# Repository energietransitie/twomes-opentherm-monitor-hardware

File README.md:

# Twomes OpenTherm Monitor Shield hardware

This repository contains the open hardware design files for the Twomes OpenTherm Monitor device, consisting of:
* a Twomes OpenTherm Monitor Shield with a [WeMos D1 Mini shield](https://www.wemos.cc/en/latest/d1_mini_shield/index.html) form factor, to be placed on;
* a WeMos D1 Mini board, such as the [LilyGO TTGO T7 Mini32 V1.3 ESP32](https://github.com/LilyGO/ESP32-MINI-32-V1.3). 

The OpenTherm Monitor Shield is connected via one pluggable terminal block with screws to connect one wire pair leading to a [boiler that supports OpenTherm](https://www.otgw.tclcode.com/matrix.cgi#boilers) and via another one pluggable terminal block with screws to connect another wire pair leading to a [thermostat that supports OpenTherm](https://www.otgw.tclcode.com/matrix.cgi#thermostats). The Twomes OpenTherm Monitor can upload this measurement data to a Twomes server via Wi-Fi using secure HTTPS.

N.B. This is device  is NOT an OpenTherm gateway; it only monitors OpenTherm traffic and it cannot insert OpenTherm commands to the boiler or thermostat.

## Table of contents
* [General info](#general-info)
* [Producing](#producing)
* [Developing](#developing) 
* [Features](#features)
* [Status](#status)
* [License](#license)
* [Citation](#citation)
* [Credits](#credits)

## General info
This repository contains the open hardware designs files for the Twomes OpenTherm Monitor device, It also includes a `docs` folder with recent printouts of the [schematics](./docs/twomes-opentherm-monitor-hardware-sch-v2.0.pdf) and [PCB layout](./docs/twomes-opentherm-monitor-hardware-pcb-v2.0.pdf). 

The associated firmware that you can run on this device can be found in [this repository](https://github.com/energietransitie/twomes-opentherm-monitor-firmware).

## Producing

### Printed Ciruit Board
To fabricate the printed circuit board you can use various PCB services. 

The folder [pcb/jlcpcb](./pcb/jlcpcb) includes all exported files needed to have the PCBs manufactured by [JLCPCB](https://www.jlcpcb.com). Upload the [zipped gerber files](./pcb/jlcpcb/gerber/gerber-OpenThermMonitorTwomes.zip) to the [JLCPCB quote page](https://cart.jlcpcb.com/quote), select the amount of PCBs and a colour for the silkscreen. All other options can be left on default. If SMT assembly is desired, also select this option before ordering. This will take you to a page where the BOM and POS file can be uploaded. Use the files [BOM-TwomesGateway.csv](./pcb/jlcpcb/assembly/BOM-Twomes-OpenTherm-Monitor.csv) and [CPL-TwomesGateway.csv](./pcb/jlcpcb/assembly/CPL-Twomes-OpenTherm-Monitor.csv).

N.B. The pluggable terminal blocks we used (see [features](#features) are not listed the BOM-*.csv file; they need to be ordered separately other services and soldered manually.

### Enclosure
To fabricate the enclosure you can use your own 3D printer or use a 3D printing service. 

The folder [enclosure/fabrication](./enclosure/fabrication) contains exported STL files for the [case](./enclosure/fabrication/twomes-opentherm-monitor-enclosure-case.stl) and [lid](./enclosure/twomes-opentherm-monitor-enclosure-lid.stl) of the Twomes OpenTherm Monitor. The STL files can be imported into any slicer and turned into G-Code for a 3D printer.

## Developing

### Printed Circuit Board
To change the hardware design of the PCB, you need:
* [KiCad](https://www.kicad.org/download/) installed to change te PCB design. 

The KiCad source files of the PCB can be found in the folder [pcb](./pcb).

To convert the PCBs into a format suitable for fabrication, consult the webpage of your PCB manufacturer of choice. For example, see the [JLCPCB guide on how to export Gerbers](https://support.jlcpcb.com/article/149-how-to-generate-gerber-and-drill-files-in-kicad) and the  [JLCPCB guide how to export the BOM and POS files](https://support.jlcpcb.com/article/84-how-to-generate-the-bom-and-centroid-file-from-kicad). You may also use a KiCad plug-in for this purpose such as [kicad-jlcpcb-tools](https://github.com/Bouni/kicad-jlcpcb-tools).

### Enclosure
To change the hardware design of the enclosure, you need either:
* [Autodesk Fusion 360](https://www.kicad.org/download/) installed (Autodesk provides 30 day free trials and [free one-year educational access](https://www.autodesk.com/education/edu-software/overview?sorting=featured&filters=individual) to its products and services for eligible students, teachers and research staff); 
* or [FreeCAD](https://www.freecadweb.org/), an open source alternative.

The source files of the enclosure can be found in the folder [enclosure](./enclosure). We include both .f3d source files and .step source files we obtained after conversion.

## Features
The Twomes OpenTherm Monitor Shield is a [WeMos D1 Mini shield](https://www.wemos.cc/en/latest/d1_mini_shield/index.html) that features the following main hardware components:
* two terminal blocks [CTB9209/2](https://nl.farnell.com/camdenboss/ctb9209-2/terminal-block-pluggable-2pos/dp/2493642), pluggable into terminal block headers [CTB9359/2](https://nl.farnell.com/camdenboss/ctb9359-2/terminal-block-header-2pos-th/dp/2493694) (one for thermostat, one for boiler), each with two positions;
* two optocouplers that electrically separate the OpenTherm circuit on the shield from the monitoring logic on the shield and the main board: the OpenTherm communication between thermostat and boiler still works even if the main board receives no power via its micro USB port or has crashed;
* recessed button that is positioned behind a pinhole in the device enclosure, which allows the end-user to do a Wi-Fi reset.

To-do:
* change design and JLCPCB files to take advantage of the new [one-sided hand-soldering option for through-hole parts](https://jlcpcb.com/smt-assembly) for the pluggable terminal blocks `J1` and `J2` and the pin headers `P1` and `P2`;

## Status
Project is: _in progress_

## License
The hardware designs in this repository are available under the [CERN-OHL-P v2 license](./LICENSE), Copyright 2022 [Research group Energy Transition, Windesheim University of Applied Sciences](https://windesheim.nl/energietransitie)

## Citation

If you use this repository in your research or work, please cite the following pre-print, which describes the overall NeedForHeat DataGear system of which this repository is a part:

> Ter Hofte, H., & van Ravenzwaaij, N. (2025). *NeedForHeat DataGear: An Open Monitoring System to Accelerate the Residential Heating Transition*. arXiv preprint arXiv:2509.06927. https://doi.org/10.48550/arXiv.2509.06927

**Note:** This is a pre-print submitted on 8 Sep 2025 and has not yet been peer-reviewed. For the full paper, see [https://arxiv.org/abs/2509.06927](https://arxiv.org/abs/2509.06927).

## Credits
This open hardware design is a collaborative effort of:
* Marco Winkelman · [@MarcoW71](https://github.com/MarcoW71)
* Sjors Smit · [@Shorts1999](https://github.com/Shorts1999)

Thanks also go to:
* Henri ter Hofte · [@henriterhofte](https://github.com/henriterhofte)
We use and gratefully acknowlegde the efforts of the makers of the following designs:

* [KiCad Libraries](https://kicad.github.io/), by the KiCad Development Team, licensed under [an adapted version of the CC-BY-SA 4.0 License](https://www.kicad.org/libraries/license/)
* [Opentherm-monitor](https://www.domoticaforum.eu/uploaded/bwired/Open-Termostaat.pdf). In <i>Elektuur, 7-8/2001, pp. 22-23.

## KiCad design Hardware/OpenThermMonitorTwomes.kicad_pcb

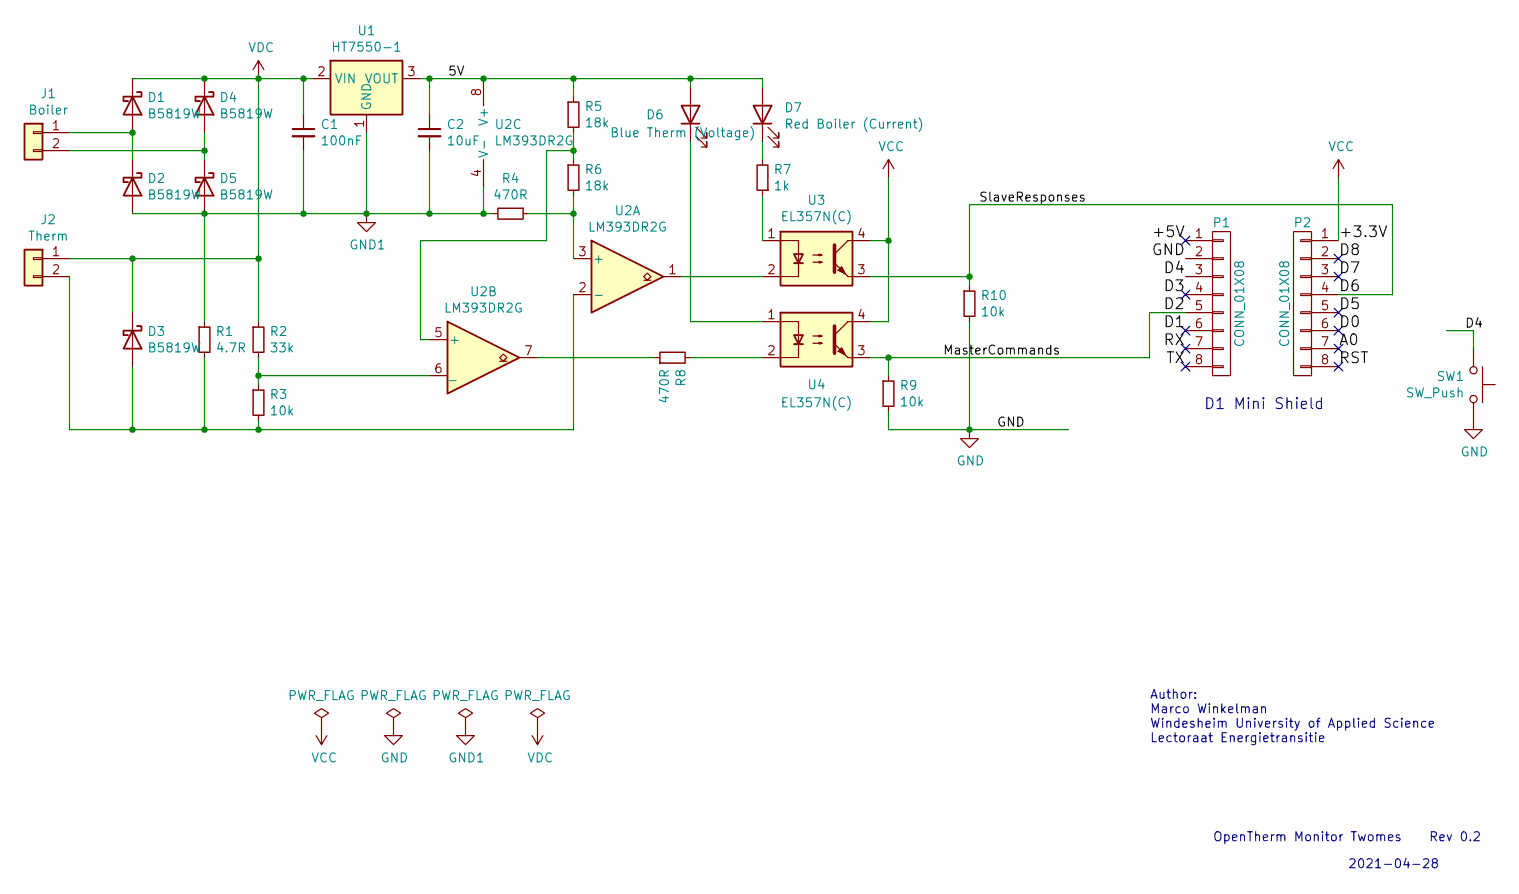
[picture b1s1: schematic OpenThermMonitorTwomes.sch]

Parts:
C1: 100nF; C_0603_1608Metric; LCSC C14663
C2: 10uF; C_0603_1608Metric; LCSC C19702
D1, D2, D3, D4, D5: B5819W; D_SOD-123; LCSC C8598
D6: Blue Therm (Voltage); LED_0805_2012Metric; LCSC C2293
D7: Red Boiler (Current); LED_0805_2012Metric; LCSC C84256
J1: Boiler; TerminalBlock_Phoenix_MKDS-1,5-2_1x02_P5.00mm_Horizontal
J2: Therm; TerminalBlock_Phoenix_MKDS-1,5-2_1x02_P5.00mm_Horizontal
P1, P2: CONN_01X08; D1_mini_Pin_Header
R1: 4.7R; R_0603_1608Metric; LCSC C23164
R2: 33k; R_0603_1608Metric; LCSC C4216
R3, R9, R10: 10k; R_0603_1608Metric; LCSC C25804
R4, R8: 470R; R_0603_1608Metric; LCSC C23179
R5, R6: 18k; R_0603_1608Metric; LCSC C25810
R7: 1k; R_0603_1608Metric; LCSC C21190
SW1: SW_Push; SW_SPST_EVQP7C; LCSC C115361
U1: HT7550-1; SOT-89-3; LCSC C16106
U2: LM393DR2G; SOIC-8_3.9x4.9mm_P1.27mm; LCSC C7955
U3, U4: EL357N(C); SO-4_4.4x3.6mm_P2.54mm; LCSC C29981

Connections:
/5V: C2.1, D6.2 (A), D7.2 (A), R5.1, U1.3 (VOUT), U2.8 (V+)
/+5V: P1.1
/A0: P2.7
/D0: P2.6
/D1: P1.6
/D2: P1.5, R9.1, U4.3
/D3: P1.4
/D4: P1.3, SW1.2
/D5: P2.5
/D6: P2.4, R10.1, U3.3
/D7: P2.3
/D8: P2.2
/RST: P2.8
/RX: P1.7
/TX: P1.8
GND: P1.2, R9.2, R10.2, SW1.1
GND1: C1.2, C2.2, D2.2 (A), D5.2 (A), R1.1, R4.2, U1.1 (GND), U2.4 (V-)
unnamed: D1.2 (A), D2.1 (K), J1.1
unnamed: D3.2 (A), J2.2, R1.2, R3.2, U2.2 (-)
unnamed: D4.2 (A), D5.1 (K), J1.2
unnamed: D6.1 (K), U4.1
unnamed: D7.1 (K), R7.2
unnamed: R2.2, R3.1, U2.6 (_)
unnamed: R4.1, R6.2, U2.3 (+)
unnamed: R5.2, R6.1, U2.5 (+)
unnamed: R7.1, U3.1
unnamed: R8.1, U2.7
unnamed: R8.2, U4.2
unnamed: U2.1, U3.2
VCC: P2.1, U3.4, U4.4
VDC: C1.1, D1.1 (K), D3.1 (K), D4.1 (K), J2.1, R2.1, U1.2 (VIN)

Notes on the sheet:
D1 Mini Shield
OpenTherm Monitor Twomes
Author: Marco Winkelman Windesheim University of Applied Science Lectoraat Energietransitie
2021-04-28
Rev 0.2

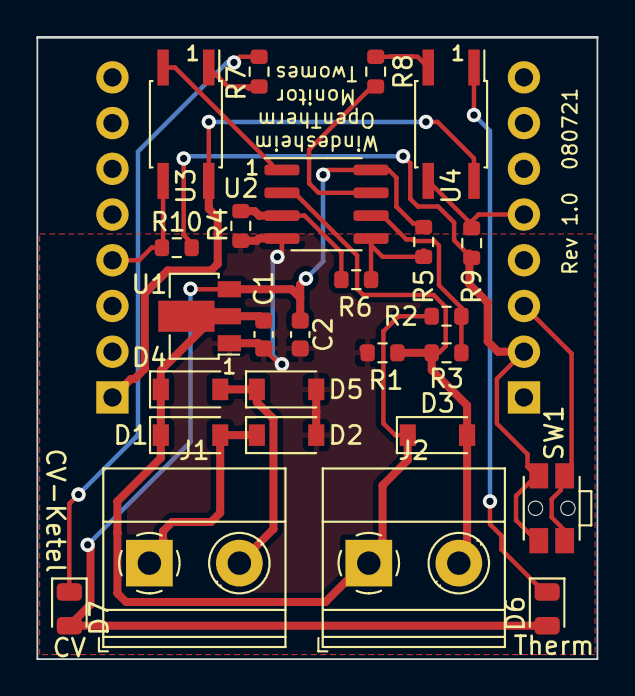
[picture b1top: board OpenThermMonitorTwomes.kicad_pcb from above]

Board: 2 copper layers, 31.1 x 34.5 mm, 28 parts (0 on the bottom side), 20 nets.

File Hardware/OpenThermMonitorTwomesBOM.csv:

Comment,Designator,Footprint,LCSC
10nF,C1,Capacitor_SMD:C_0603_1608Metric,C57112
10uF,C2,Capacitor_SMD:C_0603_1608Metric,C19702
B5819W,"D1,D2,D3,D4,D5",Diode_SMD:D_SOD-123,C8598
Blue Therm (Voltage),D6,LED_SMD:LED_0805_2012Metric,C2293
Red Boiler (Current),D7,LED_SMD:LED_0805_2012Metric,C84256
Boiler,J1,"TerminalBlock_Phoenix:TerminalBlock_Phoenix_MKDS-1,5-2_1x02_P5.00mm_Horizontal",
Therm,J2,"TerminalBlock_Phoenix:TerminalBlock_Phoenix_MKDS-1,5-2_1x02_P5.00mm_Horizontal",
CONN_01X08,"P1,P2",D1_mini:D1_mini_Pin_Header,
4.7R,R1,Resistor_SMD:R_0603_1608Metric,C23164
33k,R2,Resistor_SMD:R_0603_1608Metric,C4216
10k,"R3,R9,R10",Resistor_SMD:R_0603_1608Metric,C25804
18k,"R5,R6",Resistor_SMD:R_0603_1608Metric,C25810
1k,"R7,R8",Resistor_SMD:R_0603_1608Metric,C21190
470R,R4,Resistor_SMD:R_0603_1608Metric,C23179
SW_Push,SW1,Button_Switch_SMD:SW_SPST_EVQP7C,C115361
HT7550-1,U1,Package_TO_SOT_SMD:SOT-89-3,C16106
LM393DR2G,U2,Package_SO:SOIC-8_3.9x4.9mm_P1.27mm,C7955
EL357N(C),"U3,U4",Package_SO:SO-4_4.4x3.6mm_P2.54mm,C29981

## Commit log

2021-05-17 Update LICENSE
2021-05-17 OpenTherm HW KiCad design rev 0.2
2021-06-08 add front and back photos
2021-06-08 move frond and back image to hardware folder
2021-06-23 Create LICENSE
2021-09-22 V1.1 Fixed risetime issue
2021-09-22 Generated new position files for PCB assembly to reflect updated components in v1.1 schematic
2021-11-12 new enclosures with text
2022-01-04 directory restructure and update readme
2022-01-06 restructure repository and update README
2022-01-06 updated credits
2022-01-06 fix typo
2022-01-07 add pluggable terminal block specs
2022-09-02 Update README.md
    fix link error in readme

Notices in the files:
Hardware/OpenThermMonitorTwomes.kicad_pcb:
Licensed under CERN-OHL-P v2
